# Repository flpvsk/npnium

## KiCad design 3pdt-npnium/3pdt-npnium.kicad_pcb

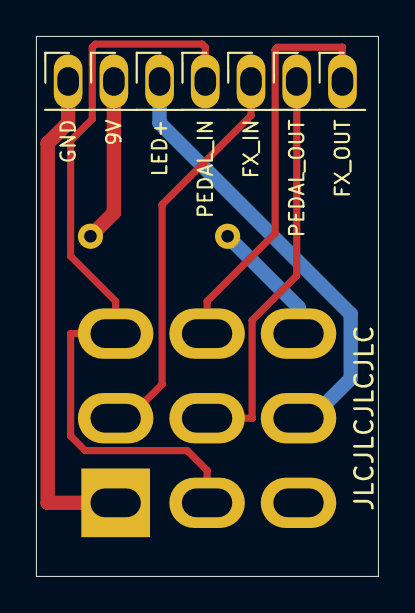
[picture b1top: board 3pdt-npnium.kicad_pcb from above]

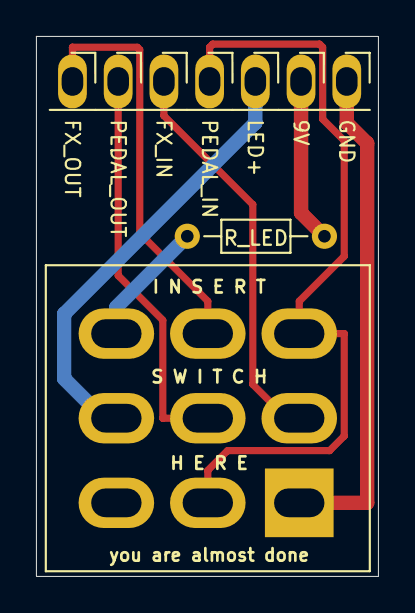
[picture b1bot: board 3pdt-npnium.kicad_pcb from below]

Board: 2 copper layers, 19.0 x 30.0 mm, 3 parts (2 on the bottom side), 8 nets.

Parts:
J1: PedalBoardHeader; BoardHeader_1x07_P2.54mm_Long_SwitchSide
R1: R_LED; R_Axial_DIN0204_L3.6mm_D1.6mm_P7.62mm_Horizontal
SW1: pedalmarkt.com; 3PDT.LUGS.FLPVSK

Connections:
+9V: J1.2, R1.1
FX_IN: J1.5, SW1.2
FX_OUT: J1.7, SW1.6
GND: J1.1, SW1.1
LED+: J1.3, SW1.8
unnamed: R1.2, SW1.9
PEDAL_IN: J1.4, SW1.3, SW1.4
PEDAL_OUT: J1.6, SW1.5

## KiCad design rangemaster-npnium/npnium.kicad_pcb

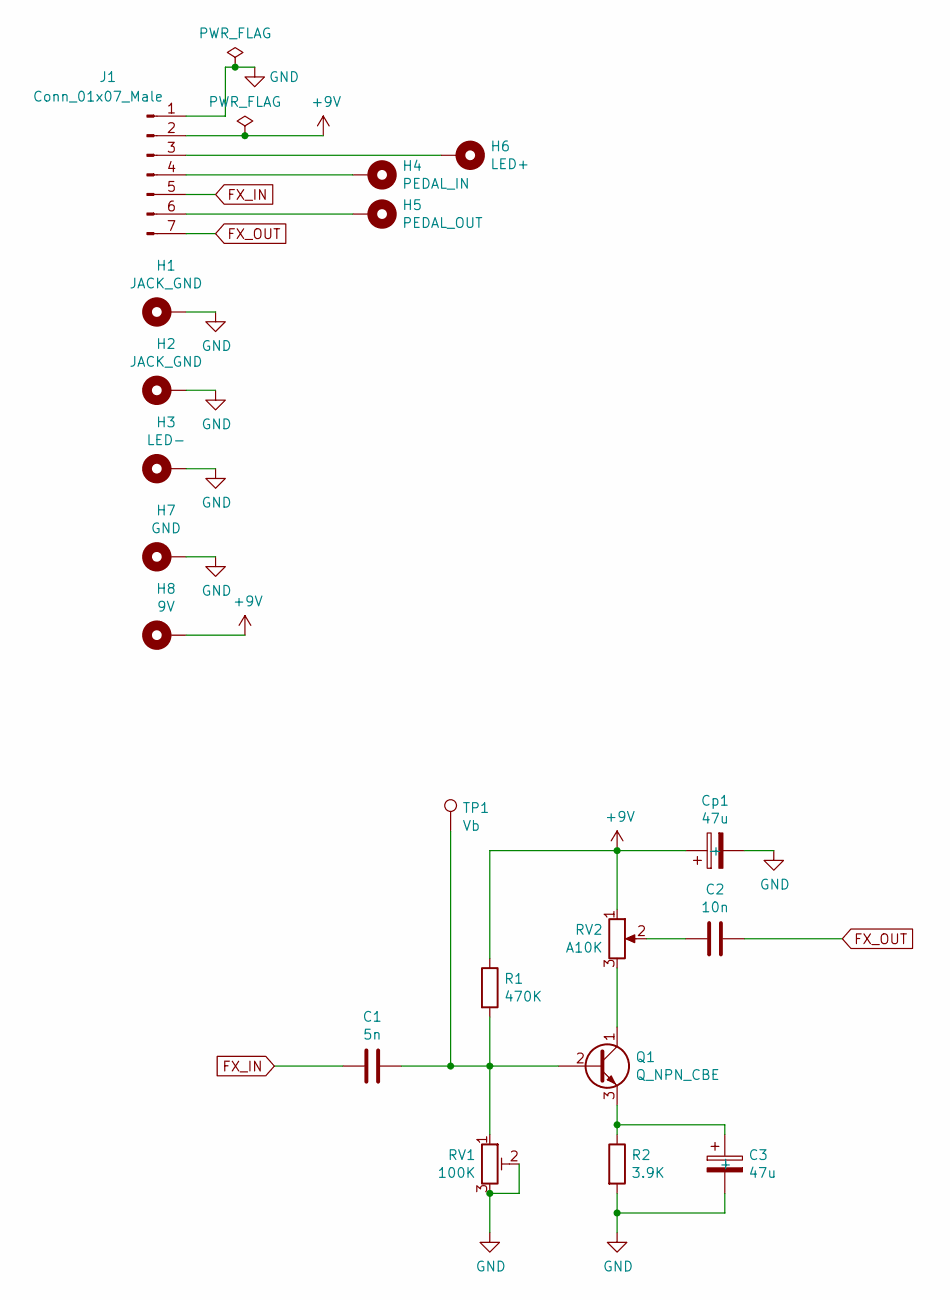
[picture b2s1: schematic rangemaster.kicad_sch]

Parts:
C1: 5n; C_Disc_D5.1mm_W3.2mm_P5.00mm
C2: 10n; C_Disc_D5.1mm_W3.2mm_P5.00mm
C3: 47u; CP_Radial_D5.0mm_P2.50mm
Cp1: 47u; CP_Radial_D5.0mm_P2.50mm
H1, H2: JACK_GND; PinHeader_1x01_P2.54mm_Long_Front_Back
H3: LED-; PinHeader_1x01_P2.54mm_Long_Front_Back
H4: PEDAL_IN; PinHeader_1x01_P2.54mm_Long_Front_Back
H5: PEDAL_OUT; PinHeader_1x01_P2.54mm_Long_Front_Back
H6: LED+; PinHeader_1x01_P2.54mm_Long_Front_Back
H7: GND; PinHeader_1x01_P2.54mm_Long_Front_Back
H8: 9V; PinHeader_1x01_P2.54mm_Long_Front_Back
J1: Conn_01x07_Male; BoardHeader_1x07_P2.54mm_Long_FXSide
Q1: Q_NPN_CBE; Transistor_TO-5_CBE_d10.1mm
R1: 470K; R_Axial_DIN0207_L6.3mm_D2.5mm_P7.62mm_Horizontal
R2: 3.9K; R_Axial_DIN0207_L6.3mm_D2.5mm_P7.62mm_Horizontal
RV1: 100K; Trim_Multi_turns
RV2: A10K; 16MM_B.MOUNT_BANZAI
TP1: Vb; TestPoint_THTPad_1.5x1.5mm_Drill0.7mm

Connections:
+9V: Cp1.1 (+), H8.1, J1.2, R1.1, RV2.1
FX_IN: C1.2, J1.5
FX_OUT: C2.1, J1.7
GND: C3.2 (-), Cp1.2 (-), H1.1, H2.1, H3.1, H7.1, J1.1, R2.2, RV1.2, RV1.3
unnamed: C1.1, Q1.2 (B), R1.2, RV1.1, TP1.1
unnamed: C2.2, RV2.2
unnamed: C3.1 (+), Q1.3 (E), R2.1
unnamed: H4.1, J1.4
unnamed: H5.1, J1.6
unnamed: H6.1, J1.3
unnamed: Q1.1 (C), RV2.3

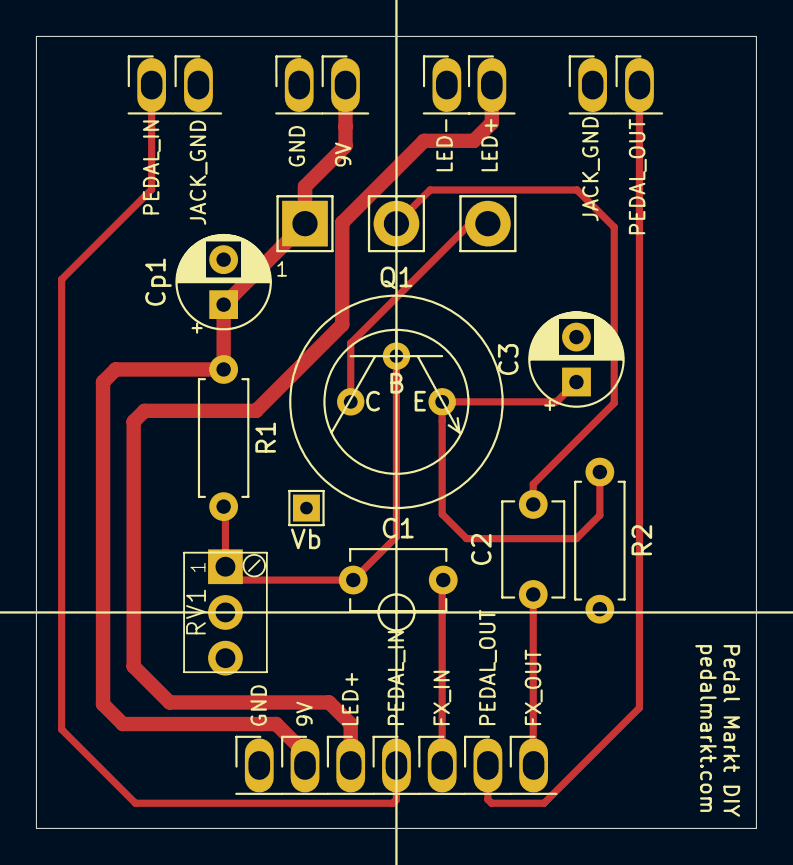
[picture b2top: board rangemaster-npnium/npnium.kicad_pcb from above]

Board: 2 copper layers, 40.0 x 44.0 mm, 21 parts (0 on the bottom side), 11 nets.

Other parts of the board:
Ref**: Val**; DC_TOP
Ref**#2: Val**; LED

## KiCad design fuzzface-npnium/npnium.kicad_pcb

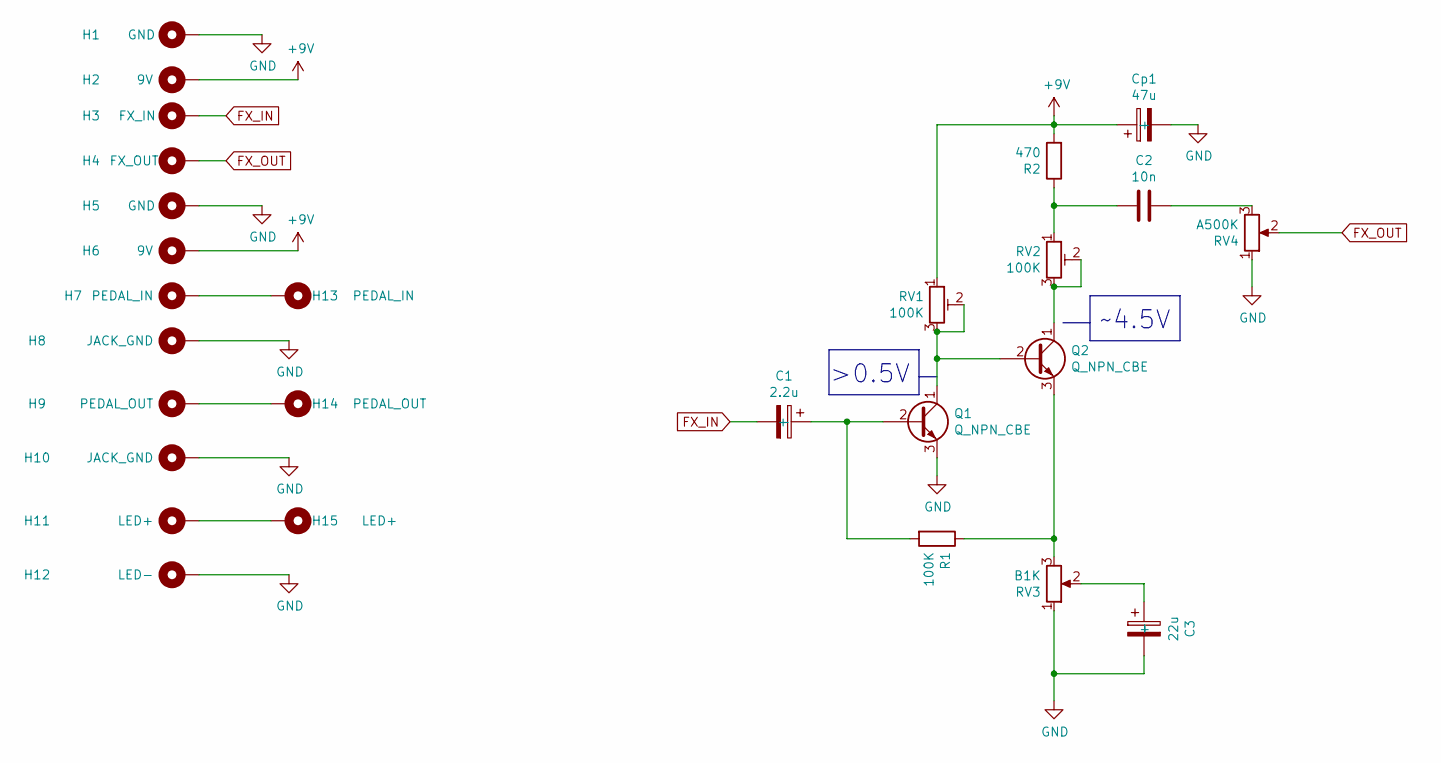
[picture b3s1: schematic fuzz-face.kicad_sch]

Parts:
C1: 2.2u; CP_Radial_D5.0mm_P2.50mm
C2: 10n; C_Disc_D5.1mm_W3.2mm_P5.00mm
C3: 22u; CP_Radial_D5.0mm_P2.50mm
Cp1: 47u; CP_Radial_D5.0mm_P2.50mm
H1, H5: GND; PinHeader_1x01_P2.54mm_Long_Front_Back
H2, H6: 9V; PinHeader_1x01_P2.54mm_Long_Front_Back
H3: FX_IN; PinHeader_1x01_P2.54mm_Long_Front_Back
H4: FX_OUT; PinHeader_1x01_P2.54mm_Long_Front_Back
H7, H13: PEDAL_IN; PinHeader_1x01_P2.54mm_Long_Front_Back
H8, H10: JACK_GND; PinHeader_1x01_P2.54mm_Long_Front_Back
H9, H14: PEDAL_OUT; PinHeader_1x01_P2.54mm_Long_Front_Back
H11, H15: LED+; PinHeader_1x01_P2.54mm_Long_Front_Back
H12: LED-; PinHeader_1x01_P2.54mm_Long_Front_Back
Q1, Q2: Q_NPN_CBE; Transistor_TO-5_CBE_d10.1mm_2
R1: 100K; R_Axial_DIN0207_L6.3mm_D2.5mm_P7.62mm_Horizontal
R2: 470; R_Axial_DIN0207_L6.3mm_D2.5mm_P7.62mm_Horizontal
RV1, RV2: 100K; Trim_Multi_turns
RV3: B1K; 16MM_B.MOUNT_BANZAI
RV4: A500K; 16MM_B.MOUNT_BANZAI

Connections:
+9V: Cp1.1 (+), H2.1, H6.1, R2.2, RV1.1
FX_IN: C1.2 (-), H3.1
FX_OUT: H4.1, RV4.2
GND: C3.2 (-), Cp1.2 (-), H1.1, H5.1, H8.1, H10.1, H12.1, Q1.3 (E), RV3.1, RV4.1
unnamed: C1.1 (+), Q1.2 (B), R1.2
unnamed: C2.1, RV4.3
unnamed: C2.2, R2.1, RV2.1
unnamed: C3.1 (+), RV3.2
unnamed: H11.1, H15.1
unnamed: H7.1, H13.1
unnamed: H9.1, H14.1
unnamed: Q1.1 (C), Q2.2 (B), RV1.2, RV1.3
unnamed: Q2.1 (C), RV2.2, RV2.3
unnamed: Q2.3 (E), R1.1, RV3.3

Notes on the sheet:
~4.5V
>0.5V

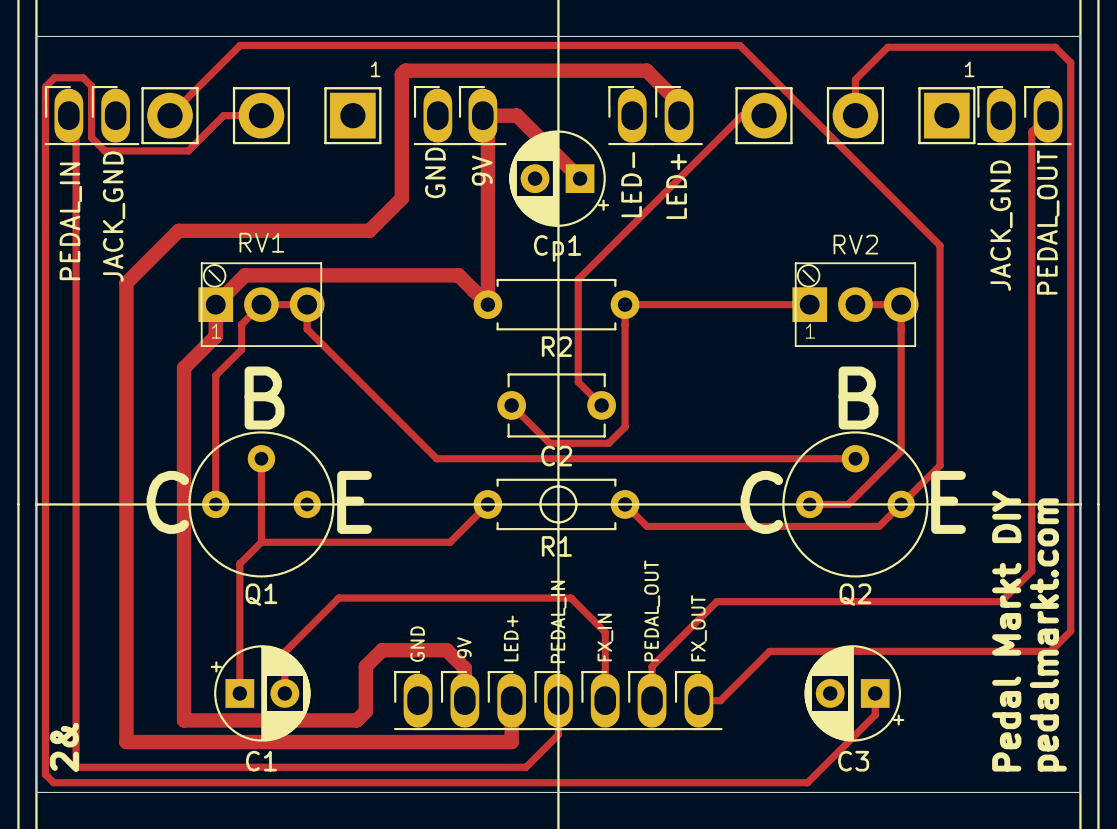
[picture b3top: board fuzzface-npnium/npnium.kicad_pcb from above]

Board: 2 copper layers, 58.0 x 42.0 mm, 29 parts (0 on the bottom side), 14 nets.

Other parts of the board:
Ref**: Val**; DC_TOP
Ref**#2: Val**; LED

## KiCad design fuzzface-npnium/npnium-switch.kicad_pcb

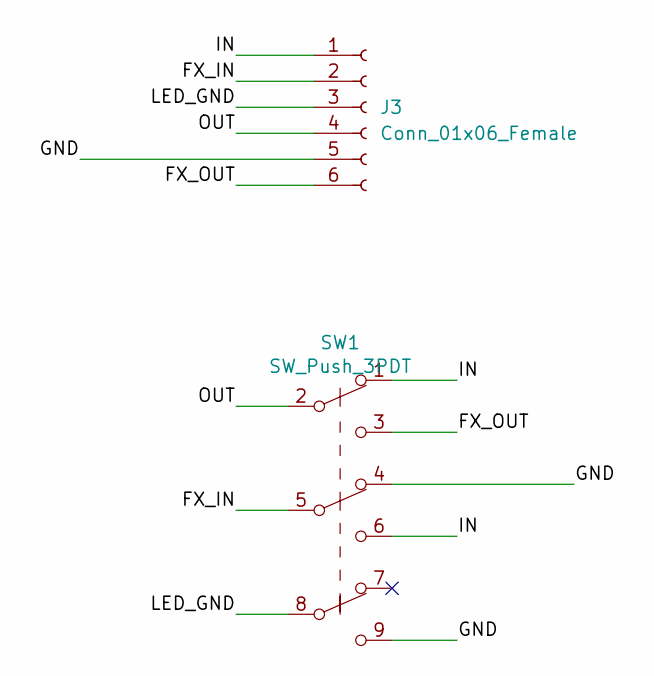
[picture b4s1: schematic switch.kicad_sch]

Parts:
J3: Conn_01x06_Female; PinHeader_1x06_P2.54mm_Vertical
SW1: SW_Push_3PDT; 3PDT.LUGS.FLPVSK

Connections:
/Switch/FX_IN: J3.2, SW1.5 (B)
/Switch/FX_OUT: J3.6, SW1.3 (C)
/Switch/GND: J3.5, SW1.4 (A), SW1.9 (C)
/Switch/IN: J3.1, SW1.1 (A), SW1.6 (C)
/Switch/LED_GND: J3.3, SW1.8 (B)
/Switch/OUT: J3.4, SW1.2 (B)

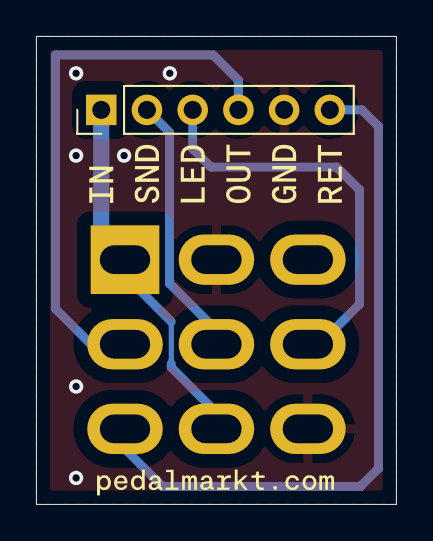
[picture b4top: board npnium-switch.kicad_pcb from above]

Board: 2 copper layers, 20.0 x 26.0 mm, 11 parts (0 on the bottom side), 6 nets.

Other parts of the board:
Ref**: Val**; DC_TOP
Ref**#2: Val**; LED
kibuzzard-6618FE8B: G***; kibuzzard-6618FE8B
kibuzzard-6618FE9C: G***; kibuzzard-6618FE9C
kibuzzard-6618FE93: G***; kibuzzard-6618FE93
kibuzzard-6618FEA0: G***; kibuzzard-6618FEA0
kibuzzard-6618FEAA: G***; kibuzzard-6618FEAA
kibuzzard-6618FEB1: G***; kibuzzard-6618FEB1
kibuzzard-66194892: G***; kibuzzard-66194892

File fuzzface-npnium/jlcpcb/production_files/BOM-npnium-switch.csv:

Comment,Designator,Footprint,LCSC
Conn_01x06_Female,J3,PinHeader_1x06_P2.54mm_Vertical,
SW_Push_3PDT,SW1,3PDT.LUGS.FLPVSK,

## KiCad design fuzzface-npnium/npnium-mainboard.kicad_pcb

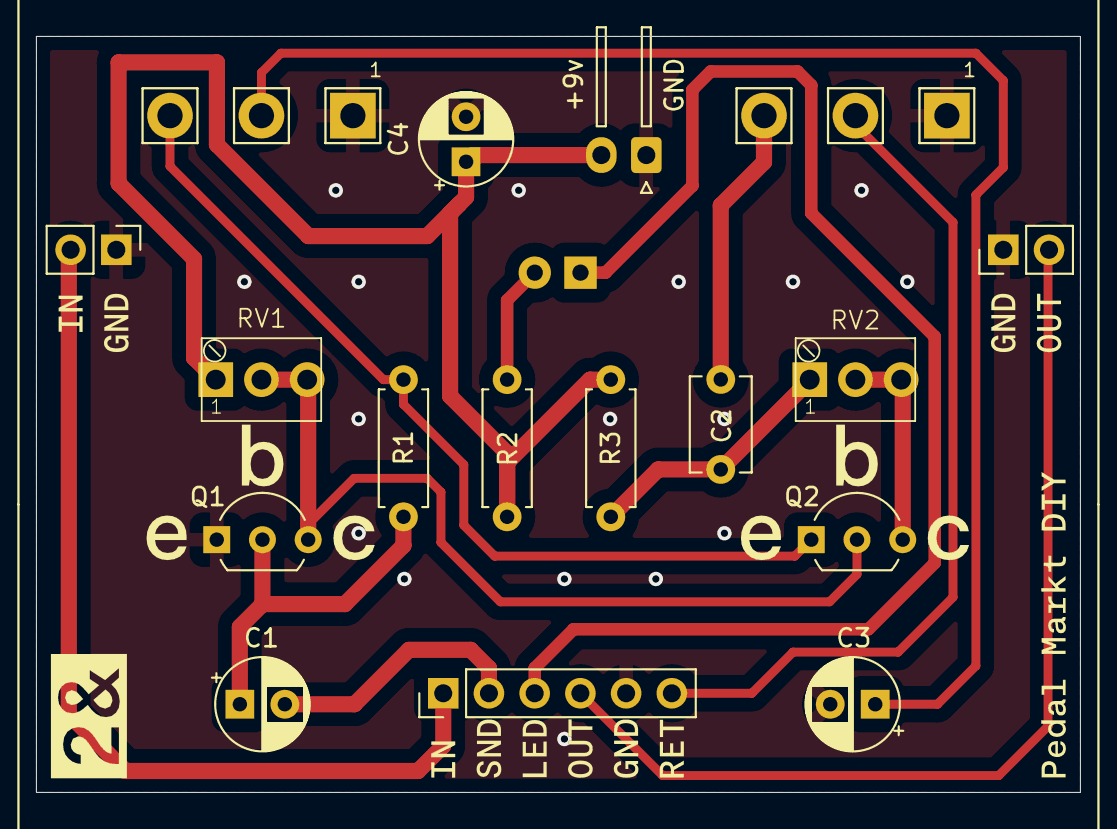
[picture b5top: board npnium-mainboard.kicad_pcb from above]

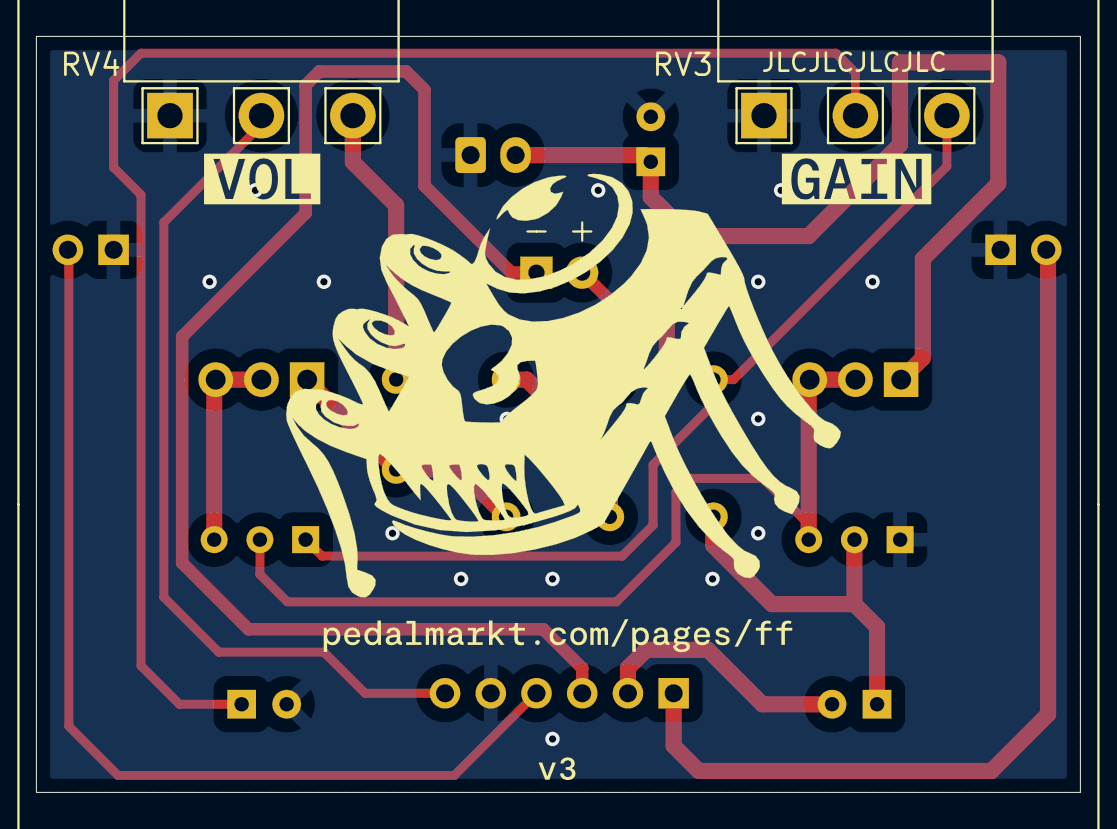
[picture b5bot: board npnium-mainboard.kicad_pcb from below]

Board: 2 copper layers, 58.0 x 42.0 mm, 42 parts (5 on the bottom side), 15 nets.

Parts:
C1: 2.2u; CP_Radial_D5.0mm_P2.50mm
C2: 10n; C_Disc_D5.1mm_W3.2mm_P5.00mm
C3: 22u; CP_Radial_D5.0mm_P2.50mm
C4: 47u; CP_Radial_D5.0mm_P2.50mm
D1: LED; LED_D5.0mm
J1: +9v; JST_XH_S2B-XH-A-1_1x02_P2.50mm_Horizontal
J2: Conn_01x06_Female; PinHeader_1x06_P2.54mm_Vertical
J4, J5: Conn_01x02_Female; PinHeader_1x02_P2.54mm_Vertical
Q1, Q2: Q_NPN_EBC; TO-92L_Inline_Wide
R1: 100K; R_Axial_DIN0207_L6.3mm_D2.5mm_P7.62mm_Horizontal
R2: Rled; R_Axial_DIN0207_L6.3mm_D2.5mm_P7.62mm_Horizontal
R3: 470; R_Axial_DIN0207_L6.3mm_D2.5mm_P7.62mm_Horizontal
RV1, RV2: 100K; Trim_Multi_turns
RV3: B1K; 16MM_B.MOUNT_BANZAI
RV4: A500K; 16MM_B.MOUNT_BANZAI
Ref**: Val**; DC_TOP
Ref**#2: Val**; LED
kibuzzard-6618FB6D, kibuzzard-6618FB6D#2: G***; kibuzzard-6618FB6D
kibuzzard-6618FB68, kibuzzard-6618FB68#2: G***; kibuzzard-6618FB68
kibuzzard-6618FB72, kibuzzard-6618FB72#2: G***; kibuzzard-6618FB72
kibuzzard-6618FE8B, kibuzzard-6618FE8B#2: G***; kibuzzard-6618FE8B
kibuzzard-6618FE9C: G***; kibuzzard-6618FE9C
kibuzzard-6618FE93: G***; kibuzzard-6618FE93
kibuzzard-6618FEA0, kibuzzard-6618FEA0#2: G***; kibuzzard-6618FEA0
kibuzzard-6618FEAA, kibuzzard-6618FEAA#2, kibuzzard-6618FEAA#3: G***; kibuzzard-6618FEAA
kibuzzard-6618FEB1: G***; kibuzzard-6618FEB1
kibuzzard-661902B4: G***; kibuzzard-661902B4
kibuzzard-661902F7: G***; kibuzzard-661902F7
kibuzzard-661903E7: G***; kibuzzard-661903E7
kibuzzard-6619005A: G***; kibuzzard-6619005A
kibuzzard-6619023A: G***; kibuzzard-6619023A
kibuzzard-66190089: G***; kibuzzard-66190089

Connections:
+9V: C4.1 (+), J1.2, R2.2, R3.2, RV1.1
FX_IN: C1.2 (-), J2.2
FX_OUT: J2.6, RV4.2
GND: C3.2 (-), C4.2 (-), J1.1, J2.5, J4.1, J5.1, Q1.1 (E), RV3.1, RV4.1
IN: J2.1, J4.2
LED_GND: D1.1 (K), J2.3
unnamed: C1.1 (+), Q1.2 (B), R1.2
unnamed: C2.1, RV4.3
unnamed: C2.2, R3.1, RV2.1
unnamed: C3.1 (+), RV3.2
unnamed: D1.2 (A), R2.1
unnamed: Q1.3 (C), Q2.2 (B), RV1.2, RV1.3
unnamed: Q2.1 (E), R1.1, RV3.3
unnamed: Q2.3 (C), RV2.2, RV2.3
OUT: J2.4, J5.2

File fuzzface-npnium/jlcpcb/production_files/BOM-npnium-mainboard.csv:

Comment,Designator,Footprint,LCSC
A500K,RV4,16MM_B.MOUNT_BANZAI,
B1K,RV3,16MM_B.MOUNT_BANZAI,
10n,C2,C_Disc_D5.1mm_W3.2mm_P5.00mm,
47u,C4,CP_Radial_D5.0mm_P2.50mm,
100K,R1,R_Axial_DIN0207_L6.3mm_D2.5mm_P7.62mm_Horizontal,
470,R3,R_Axial_DIN0207_L6.3mm_D2.5mm_P7.62mm_Horizontal,
100K,RV2,Trim_Multi_turns,
22u,C3,CP_Radial_D5.0mm_P2.50mm,
2.2u,C1,CP_Radial_D5.0mm_P2.50mm,
100K,RV1,Trim_Multi_turns,
Rled,R2,R_Axial_DIN0207_L6.3mm_D2.5mm_P7.62mm_Horizontal,
+9v,J1,JST_XH_S2B-XH-A-1_1x02_P2.50mm_Horizontal,
Conn_01x06_Female,J2,PinHeader_1x06_P2.54mm_Vertical,
Q_NPN_EBC,Q1,TO-92L_Inline_Wide,
Conn_01x02_Female,J4,PinHeader_1x02_P2.54mm_Vertical,
Q_NPN_EBC,Q2,TO-92L_Inline_Wide,
Conn_01x02_Female,J5,PinHeader_1x02_P2.54mm_Vertical,
LED,D1,LED_D5.0mm,

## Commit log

2021-09-14 Init
2021-10-24 Before v2
2021-11-26 Migrating transistor footprint
2024-04-11 Gitignore
